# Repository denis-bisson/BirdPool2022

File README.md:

# BirdPool2022
Little "C" complete program to dump in a Microchip PIC18F1330 to control water valve for a bird bath.

Basically there is like a water fountain and birds like to take a bath there. 
Unfortunately, as they keep playing in the water, the water are throw outside and ultimately the bath is missing water. 
The little projet is to have an electric valve control by a little PIC18F1330 to control that valve to add water when necessary. 
There are two level switches for the water to help to determine when we are missing water and when we added enough.
More details to be added later.

# Timeline 
2021-12-27 @ 22:00:00 - Ordered the few parts I don't have in inventory at home like the relay, the terminal blocks and the blue diode. 
2021-12-27 @ 22:00:01 - Played a little with the 3D board preview. 

2021-12-26 @ 16:47:00 - Ordered three PCB prototypes from [OSH PARK](https://oshpark.com/).

2021-12-24 @ 22:35:00 - Begin the schematic and PCB drawings 

2021-12-22 @ 22:07:00 - Prototype to test the initial program with a PIC18F1330

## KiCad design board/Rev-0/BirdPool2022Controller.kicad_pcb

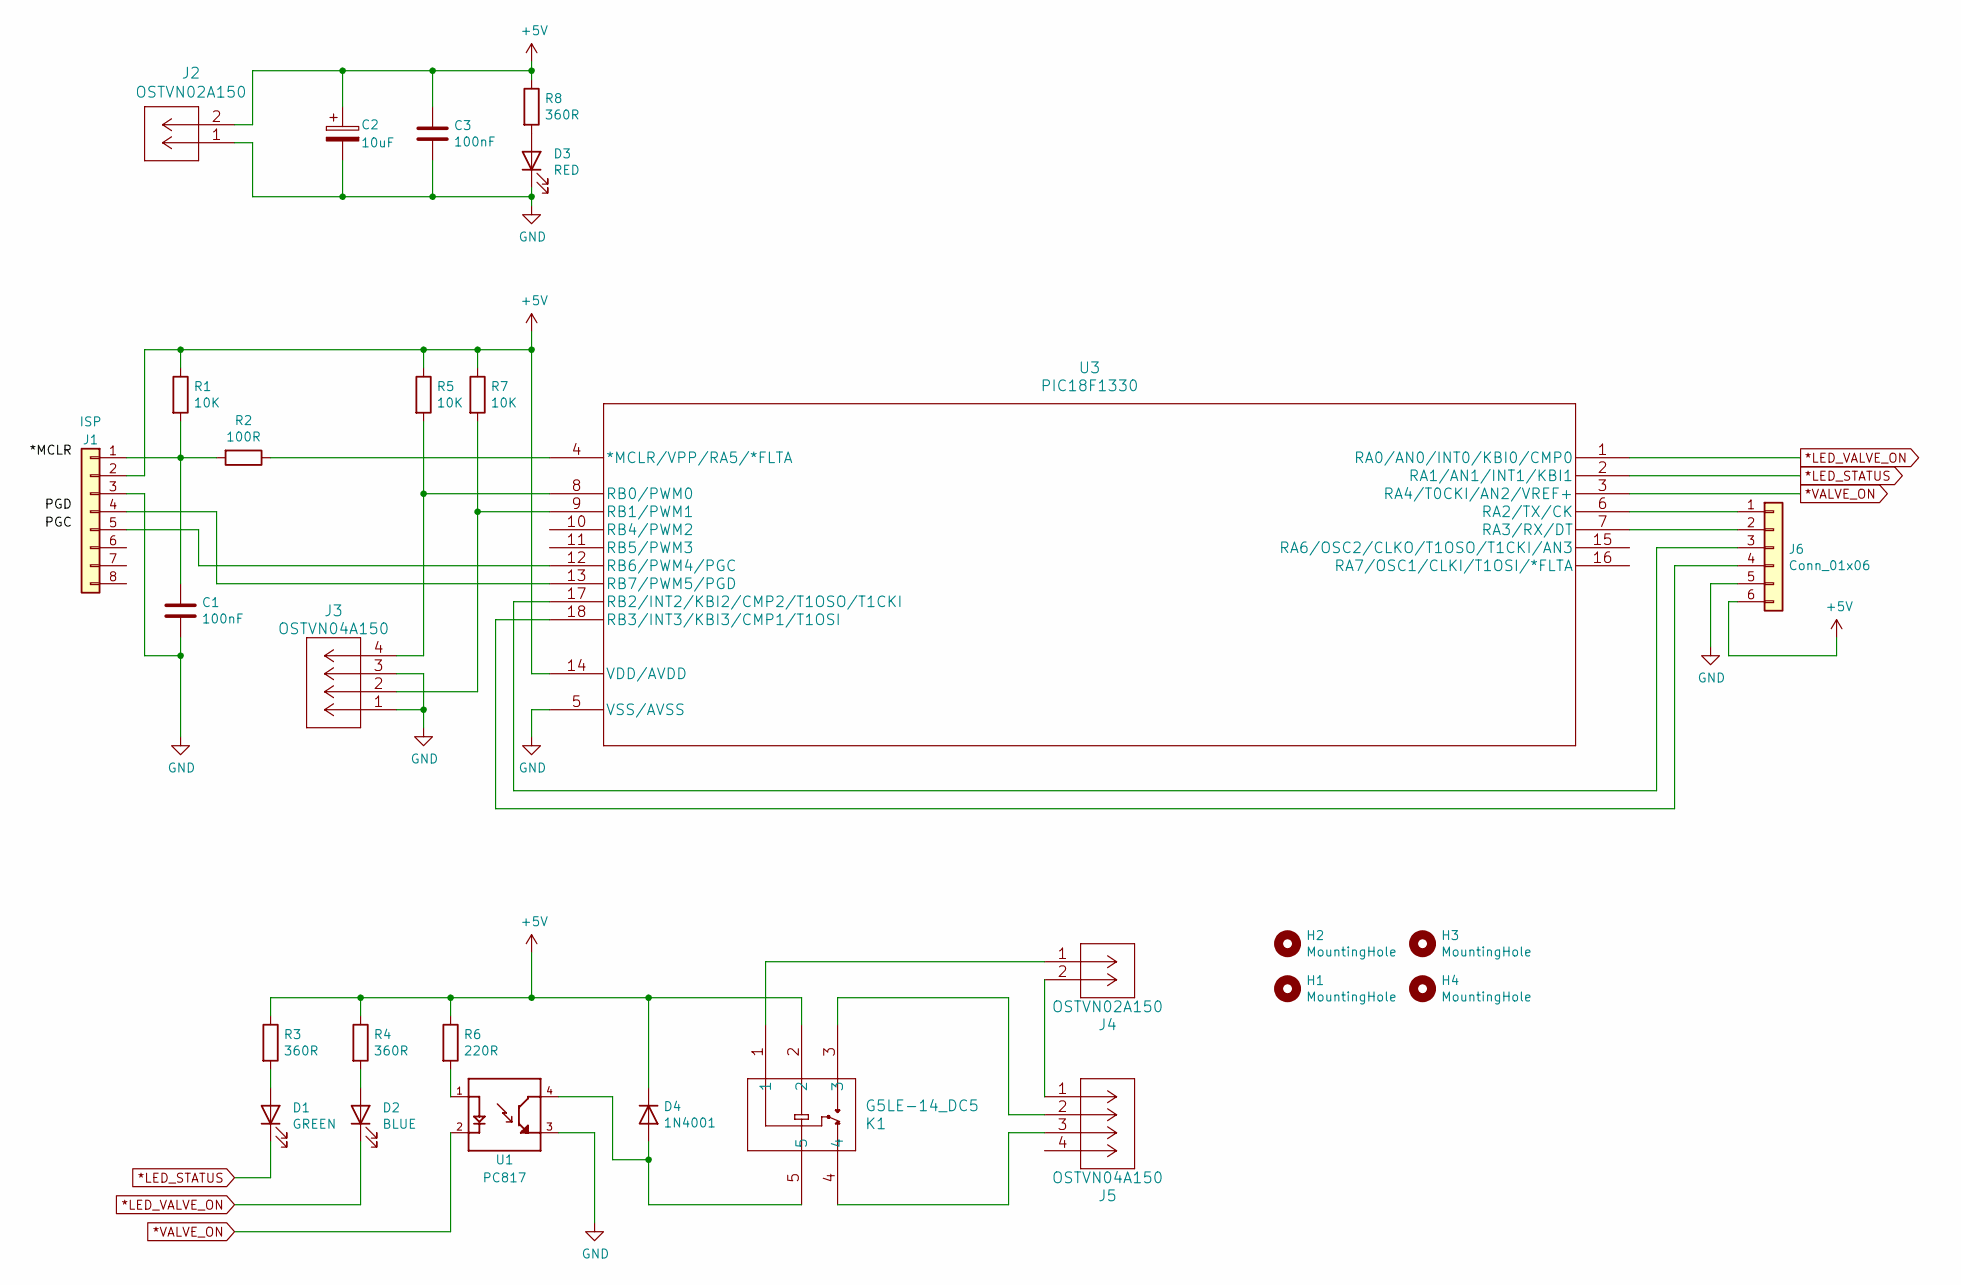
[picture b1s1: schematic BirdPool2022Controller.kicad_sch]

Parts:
C1, C3: 100nF; C_Disc_D4.3mm_W1.9mm_P5.00mm
C2: 10uF; CP_Radial_D4.0mm_P2.00mm
D1: GREEN; LED_D5.0mm
D2: BLUE; LED_D5.0mm
D3: RED; LED_D5.0mm
D4: 1N4001; D_DO-41_SOD81_P10.16mm_Horizontal
H1, H2, H3, H4: MountingHole; MountingHole_2.5mm
J1: ISP; PinHeader_1x08_P2.54mm_Vertical
J2, J4: OSTVN02A150; CONN_OSTVN02A150_OST
J3, J5: OSTVN04A150; CONN_OSTVN04A150_OST
J6: Conn_01x06; PinHeader_1x06_P2.54mm_Vertical
K1: G5LE-14_DC5; RELAY_G5LE-1_DC5_OMR
R1, R5, R7: 10K; R_Axial_DIN0207_L6.3mm_D2.5mm_P10.16mm_Horizontal
R2: 100R; R_Axial_DIN0207_L6.3mm_D2.5mm_P10.16mm_Horizontal
R3, R4, R8: 360R; R_Axial_DIN0207_L6.3mm_D2.5mm_P10.16mm_Horizontal
R6: 220R; R_Axial_DIN0207_L6.3mm_D2.5mm_P10.16mm_Horizontal
U1: PC817; DIP810W50P254L470H446Q4
U3: PIC18F1330; PDIP18_300MC_MCH

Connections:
*LED_STATUS: D1.1 (K), U3.2 (RA1/AN1/INT1/KBI1)
*LED_VALVE_ON: D2.1 (K), U3.1 (RA0/AN0/INT0/KBI0/CMP0)
*VALVE_ON: U1.2, U3.3 (RA4/T0CKI/AN2/VREF+)
+5V: C2.1, C3.1, D4.1 (K), J1.2, J2.2, J6.6, K1.2, R1.1, R3.1, R4.1, R5.1, R6.1, R7.1, R8.1, U3.14 (VDD/AVDD)
GND: C1.2, C2.2, C3.2, D3.1 (K), J1.3, J2.1, J3.1, J3.3, J6.5, U1.3, U3.5 (VSS/AVSS)
unnamed: C1.1, J1.1, R1.2, R2.2
unnamed: D1.2 (A), R3.2
unnamed: D2.2 (A), R4.2
unnamed: D3.2 (A), R8.2
unnamed: D4.2 (A), K1.5, U1.4
unnamed: J1.4, U3.13 (RB7/PWM5/PGD)
unnamed: J1.5, U3.12 (RB6/PWM4/PGC)
unnamed: J3.2, R7.2, U3.9 (RB1/PWM1)
unnamed: J3.4, R5.2, U3.8 (RB0/PWM0)
unnamed: J4.1, K1.1
unnamed: J4.2, J5.1
unnamed: J5.2, K1.3
unnamed: J5.3, K1.4
unnamed: J6.1, U3.6 (RA2/TX/CK)
unnamed: J6.2, U3.7 (RA3/RX/DT)
unnamed: J6.3, U3.17 (RB2/INT2/KBI2/CMP2/T1OSO/T1CKI)
unnamed: J6.4, U3.18 (RB3/INT3/KBI3/CMP1/T1OSI)
unnamed: R2.1, U3.4 (*MCLR/VPP/RA5/*FLTA)
unnamed: R6.2, U1.1

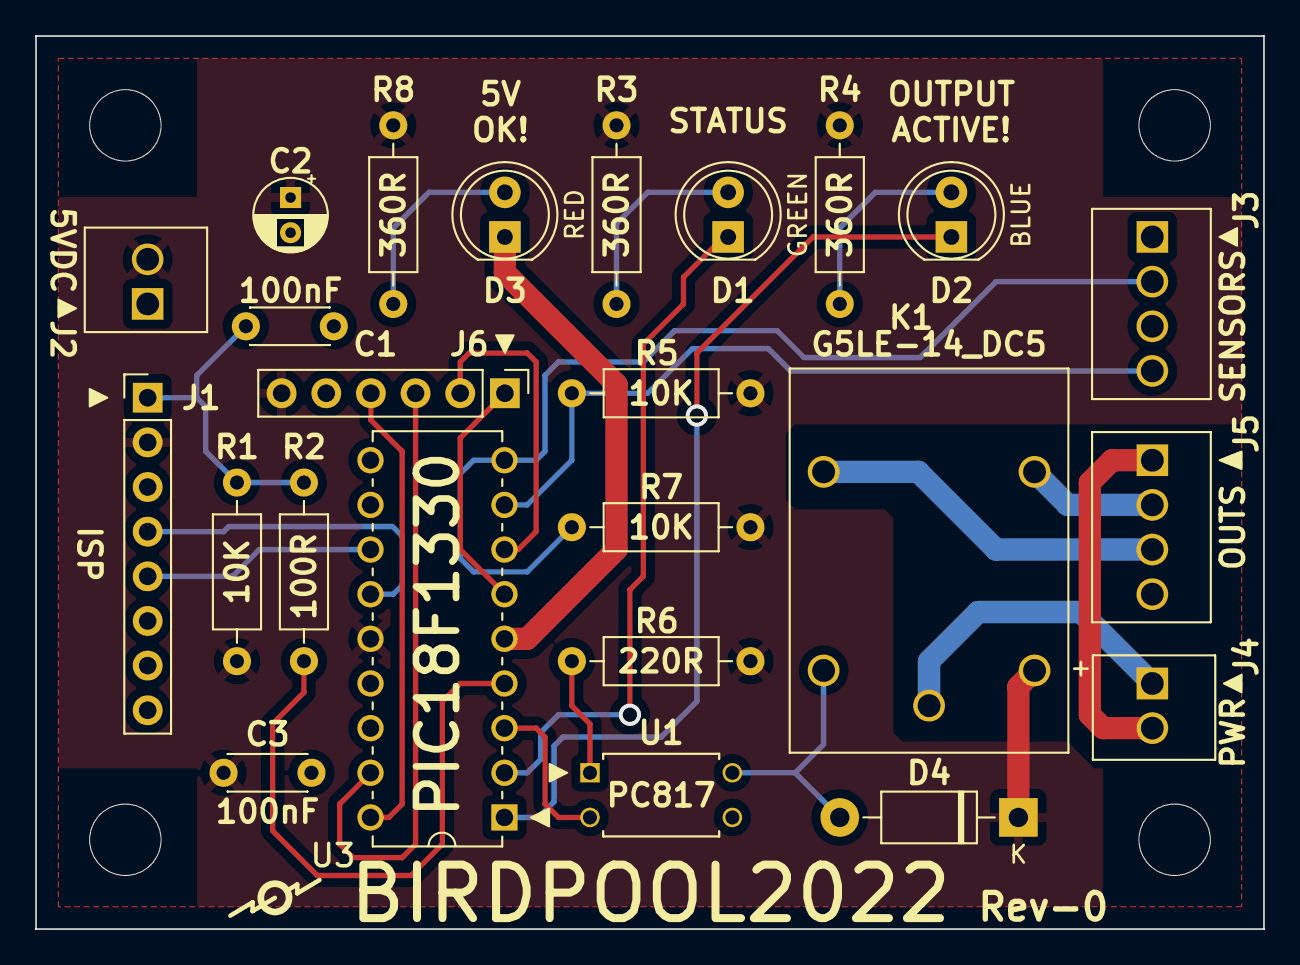
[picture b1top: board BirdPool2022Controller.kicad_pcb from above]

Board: 2 copper layers, 69.8 x 50.8 mm, 28 parts (0 on the bottom side), 24 nets.

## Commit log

2021-12-23 First commmit
    ADD: Source added. Slowly began prototype.
2021-12-23 ADD: Test to see if we can add an image in the initial README.md
2021-12-23 ADD: New picture for the ReadMe on the first page
    Just to have something on the time line.
2021-12-23 CHG: The order of picture was changed to maybe a better positions.
2021-12-23 CHG: To have "Timeline" written in larger font.
2021-12-23 FIX: To have the picture *below* the date
2021-12-23 CHG: Attempt number to have picture BELOW
2021-12-23 RMV: One directory that was not supposed to be.
2021-12-25 ADD: Start the schematic and the PCB
    ADD: Schematic and PCB file added. I am trying KiCad.
2021-12-25 ADD: New images added to timeline
    Essentially, these are screen capture of the schematic and PCB drawing
2021-12-25 ADD: Board routed
    ADD: Board has been routed.
    FIX: The relay has been routed with inverted connexion for the coil. This has been fixed.
    ADD: 6-pins expansion connector has been added.
2021-12-26 FIX: Arrange PCB
    ADD: Keepout area around mounting hole.
    ADD: Keepout area added around relay related traces.
    ADD: Use copper pour for both ground and power traces.
2021-12-26 Store board files in revision number directory
2021-12-26 Correction around the relay
    ADD: In code, add control of RA4 for the relay for the valve.
    ADD: In PCB, add fly wheel diode.
    CHG: Rearrange the relay area since the fly wheel diode addition.
2021-12-26 PCB ordered!
    ADD: Official Gerber file generated for the Rev-0.
    ADD: Three prototypes ordered from OSH PARKS.
    ADD: Picture of the preview of the PCB.
2021-12-26 Updated link for OSH PARK
2021-12-26 Third attempt for HTML link to OSH Park
2021-12-28 Played with the 3D preview generation
2021-12-28 Try to correct some title.
2021-12-28 Better time line presentation, more simple.
2022-01-03 UPD: Boards now with KiCad 6.0.0
2022-01-03 FIX: The 3D model for the board is now correct.
2022-01-08 Progression of Rev-A board
    -To be able to use a more available valves, the revision A circuit is slowly coming in place. We need to generate 24V from the 5V, and also being able to control the polarity of the applied 24V.
    -Schematics made with KiCad 6.0.0.
2022-01-08 Add a note for Rev-0 board
    -Add the following note for the Rev-0 board: "PC817 is not efficient enough for current required for the relay. I used instead of Darlington one, the PS2533-1-V-A. Digi-Key 559-1255-ND>.
2022-01-08 ADD: Inspiration
    -The inspiration for the 24V control circuit source has been added.

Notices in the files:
parts and their libraries:
Copyright 2021 Accelerated Designs. All rights reserved.
